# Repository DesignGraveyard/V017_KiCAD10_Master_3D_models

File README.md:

# Description

Master 3D models in KiCAD10, learn how to find 3D models online, check them instantly in your browser with a free tool, assign them to footprints, and keep your project 100% portable so your models never break when sharing.  
Finally I will show to to EXPORT your PCB assembly as a 3D file.  
Watch the YouTube Video in which I epxlain all steps in less than 10 minutes.  

# Check out the video <Click>:  

# Links:  
-Online 3D file viewer: https://3dviewer.net/  
-GrabCad library: https://grabcad.com/library  
  
Note: To download 3D files at GrabCAD you need to sign up with an email address: https://www.grabcad.com/profile/register  

# Files:  
  
Folder "KiCAD10_E-Load_PCB" contains the KiCAD PCB files as used in the tutorial video, including the RK163 step file and folder structure.

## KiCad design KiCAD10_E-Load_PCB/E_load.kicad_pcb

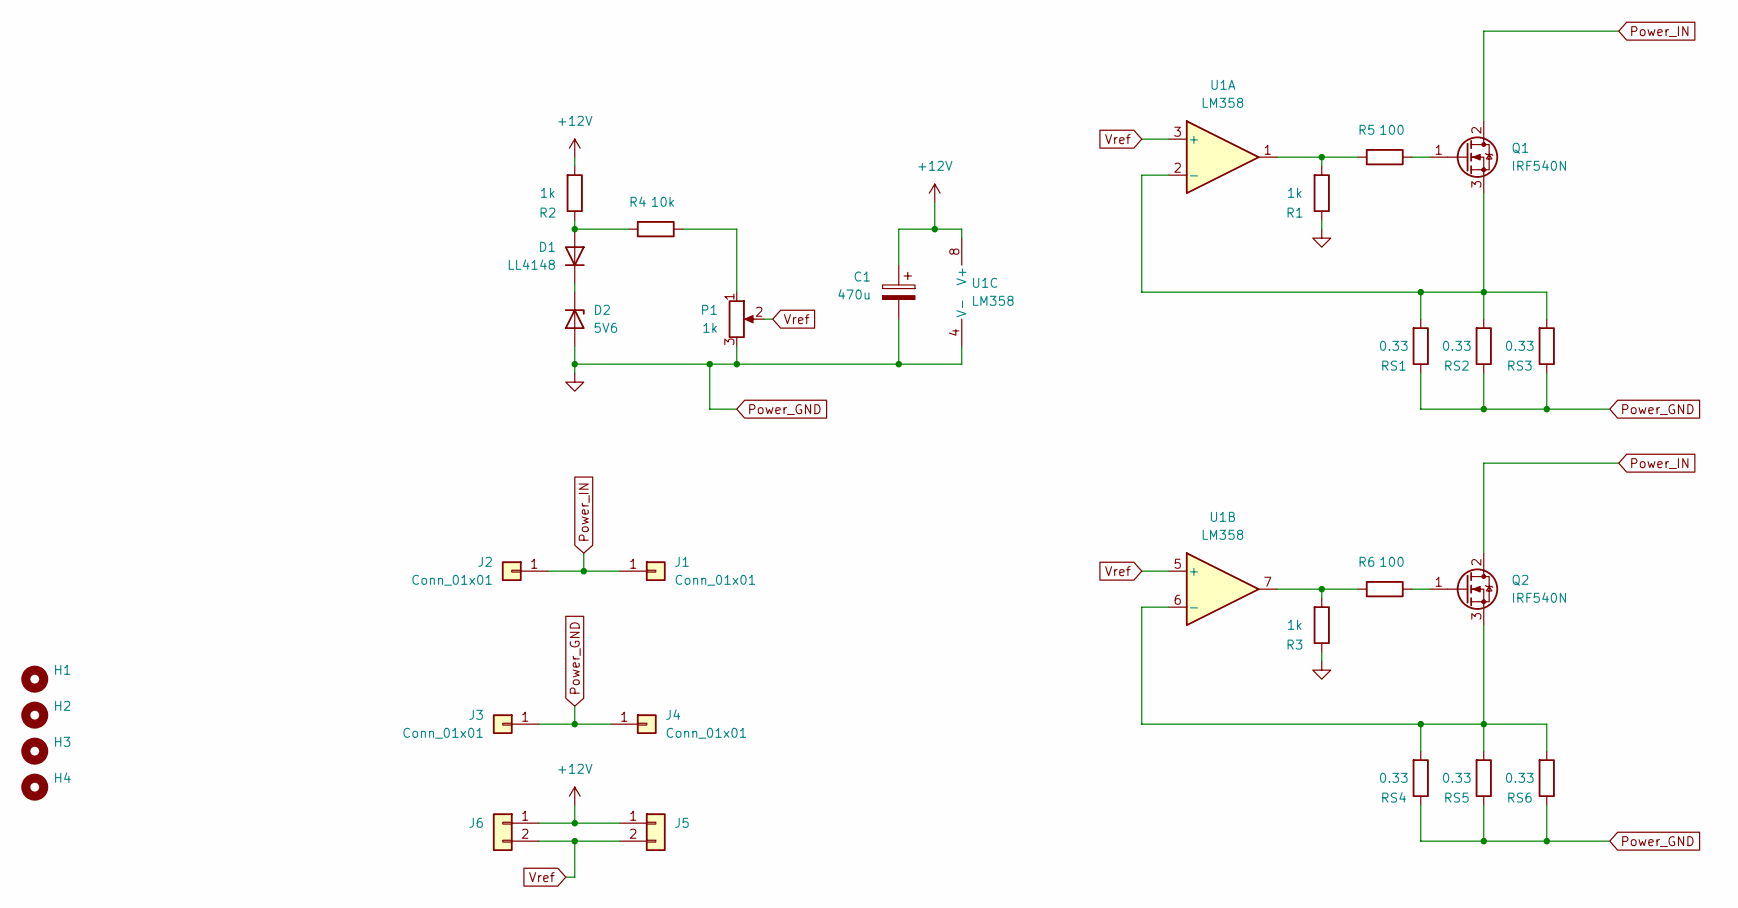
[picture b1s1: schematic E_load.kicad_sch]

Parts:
C1: 470u; CP_Radial_D8.0mm_P3.80mm
D1: LL4148; D_DO-35_SOD27_THT_and_MiniMelf_SMD_combination
D2: 5V6; D_DO-35_SOD27_THT_and_MiniMelf_SMD_combination
H1, H2, H3, H4: MountingHole; MountingHole_3.5mm
J1, J2, J3, J4: Conn_01x01; SolderWire-1.5sqmm_1x01_D1.7mm_OD3mm
J5, J6: Conn_01x02; PinHeader_1x02_P2.54mm_Vertical
P1: 1k; Potentiometer_Alps_RK163_Single_Horizontal
Q1, Q2: IRF540N; TO-220-3_Vertical
R1, R2, R3: 1k; R_THT_SMD_0805_combi
R4: 10k; R_THT_SMD_0805_combi
R5, R6: 100; R_THT_SMD_0805_combi
RS1, RS2, RS3, RS4, RS5, RS6: 0.33; R_Axial_DIN0411_L9.9mm_D3.6mm_P12.70mm_Horizontal
U1: LM358; DIP-8_W7.62mm

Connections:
+12V: C1.1, J5.1, J6.1, R2.2, U1.8 (V+)
unnamed: D1.2 (A), R2.1, R4.2
unnamed: D1.1 (K), D2.1 (K)
unnamed: P1.1, R4.1
unnamed: Q1.1 (G), R5.1
unnamed: Q1.3 (S), RS1.2, RS2.2, RS3.2, U1.2 (-)
unnamed: Q2.1 (G), R6.1
unnamed: Q2.3 (S), RS4.2, RS5.2, RS6.2, U1.6 (-)
unnamed: R1.2, R5.2, U1.1
unnamed: R3.2, R6.2, U1.7
Power_GND: C1.2, D2.2 (A), J3.1 (Pin_1_1), J4.1 (Pin_1_1), P1.3, R1.1, R3.1, RS1.1, RS2.1, RS3.1, RS4.1, RS5.1, RS6.1, U1.4 (V-)
Power_IN: J1.1 (Pin_1_1), J2.1 (Pin_1_1), Q1.2 (D), Q2.2 (D)
Vref: J5.2, J6.2, P1.2, U1.3 (+), U1.5 (+)

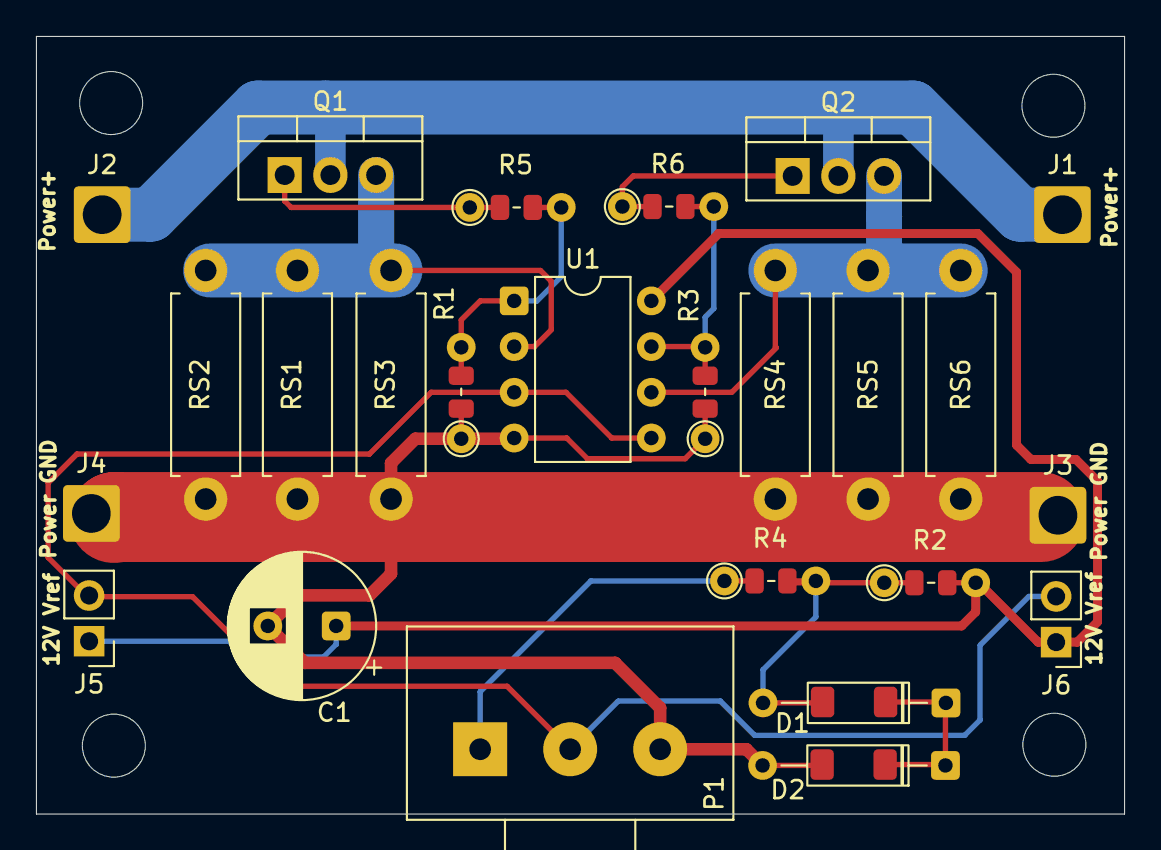
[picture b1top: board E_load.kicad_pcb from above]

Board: 2 copper layers, 60.5 x 43.2 mm, 29 parts (0 on the bottom side), 13 nets.
